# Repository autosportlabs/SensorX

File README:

DESCRIPTION:

SensorX is a breakout board designed to make it easy to integrate sensors to the analog 
inputs of RaceCapture. 

7 channels are supported to match the inputs of RaceCapture. Pullup resistors are included 
on all channels to enable resistive sensors such as temperature & fuel level; these resistors 
can be disabled by cutting traces.

Multiple ground and 5v voltage references are also provided.

The board is sized to be finished with shrink-tubing and installed in-line with wiring harness
bundles, so no explicit mounting or enclosures are necessary!

LICENSE:

The technical artifacts provided in this project is covered in a modified version of the
Creative Commons BY-SA license - see the LICENSE file for the full text.

MORE INFO:

for more information visit http://www.autosportlabs.net

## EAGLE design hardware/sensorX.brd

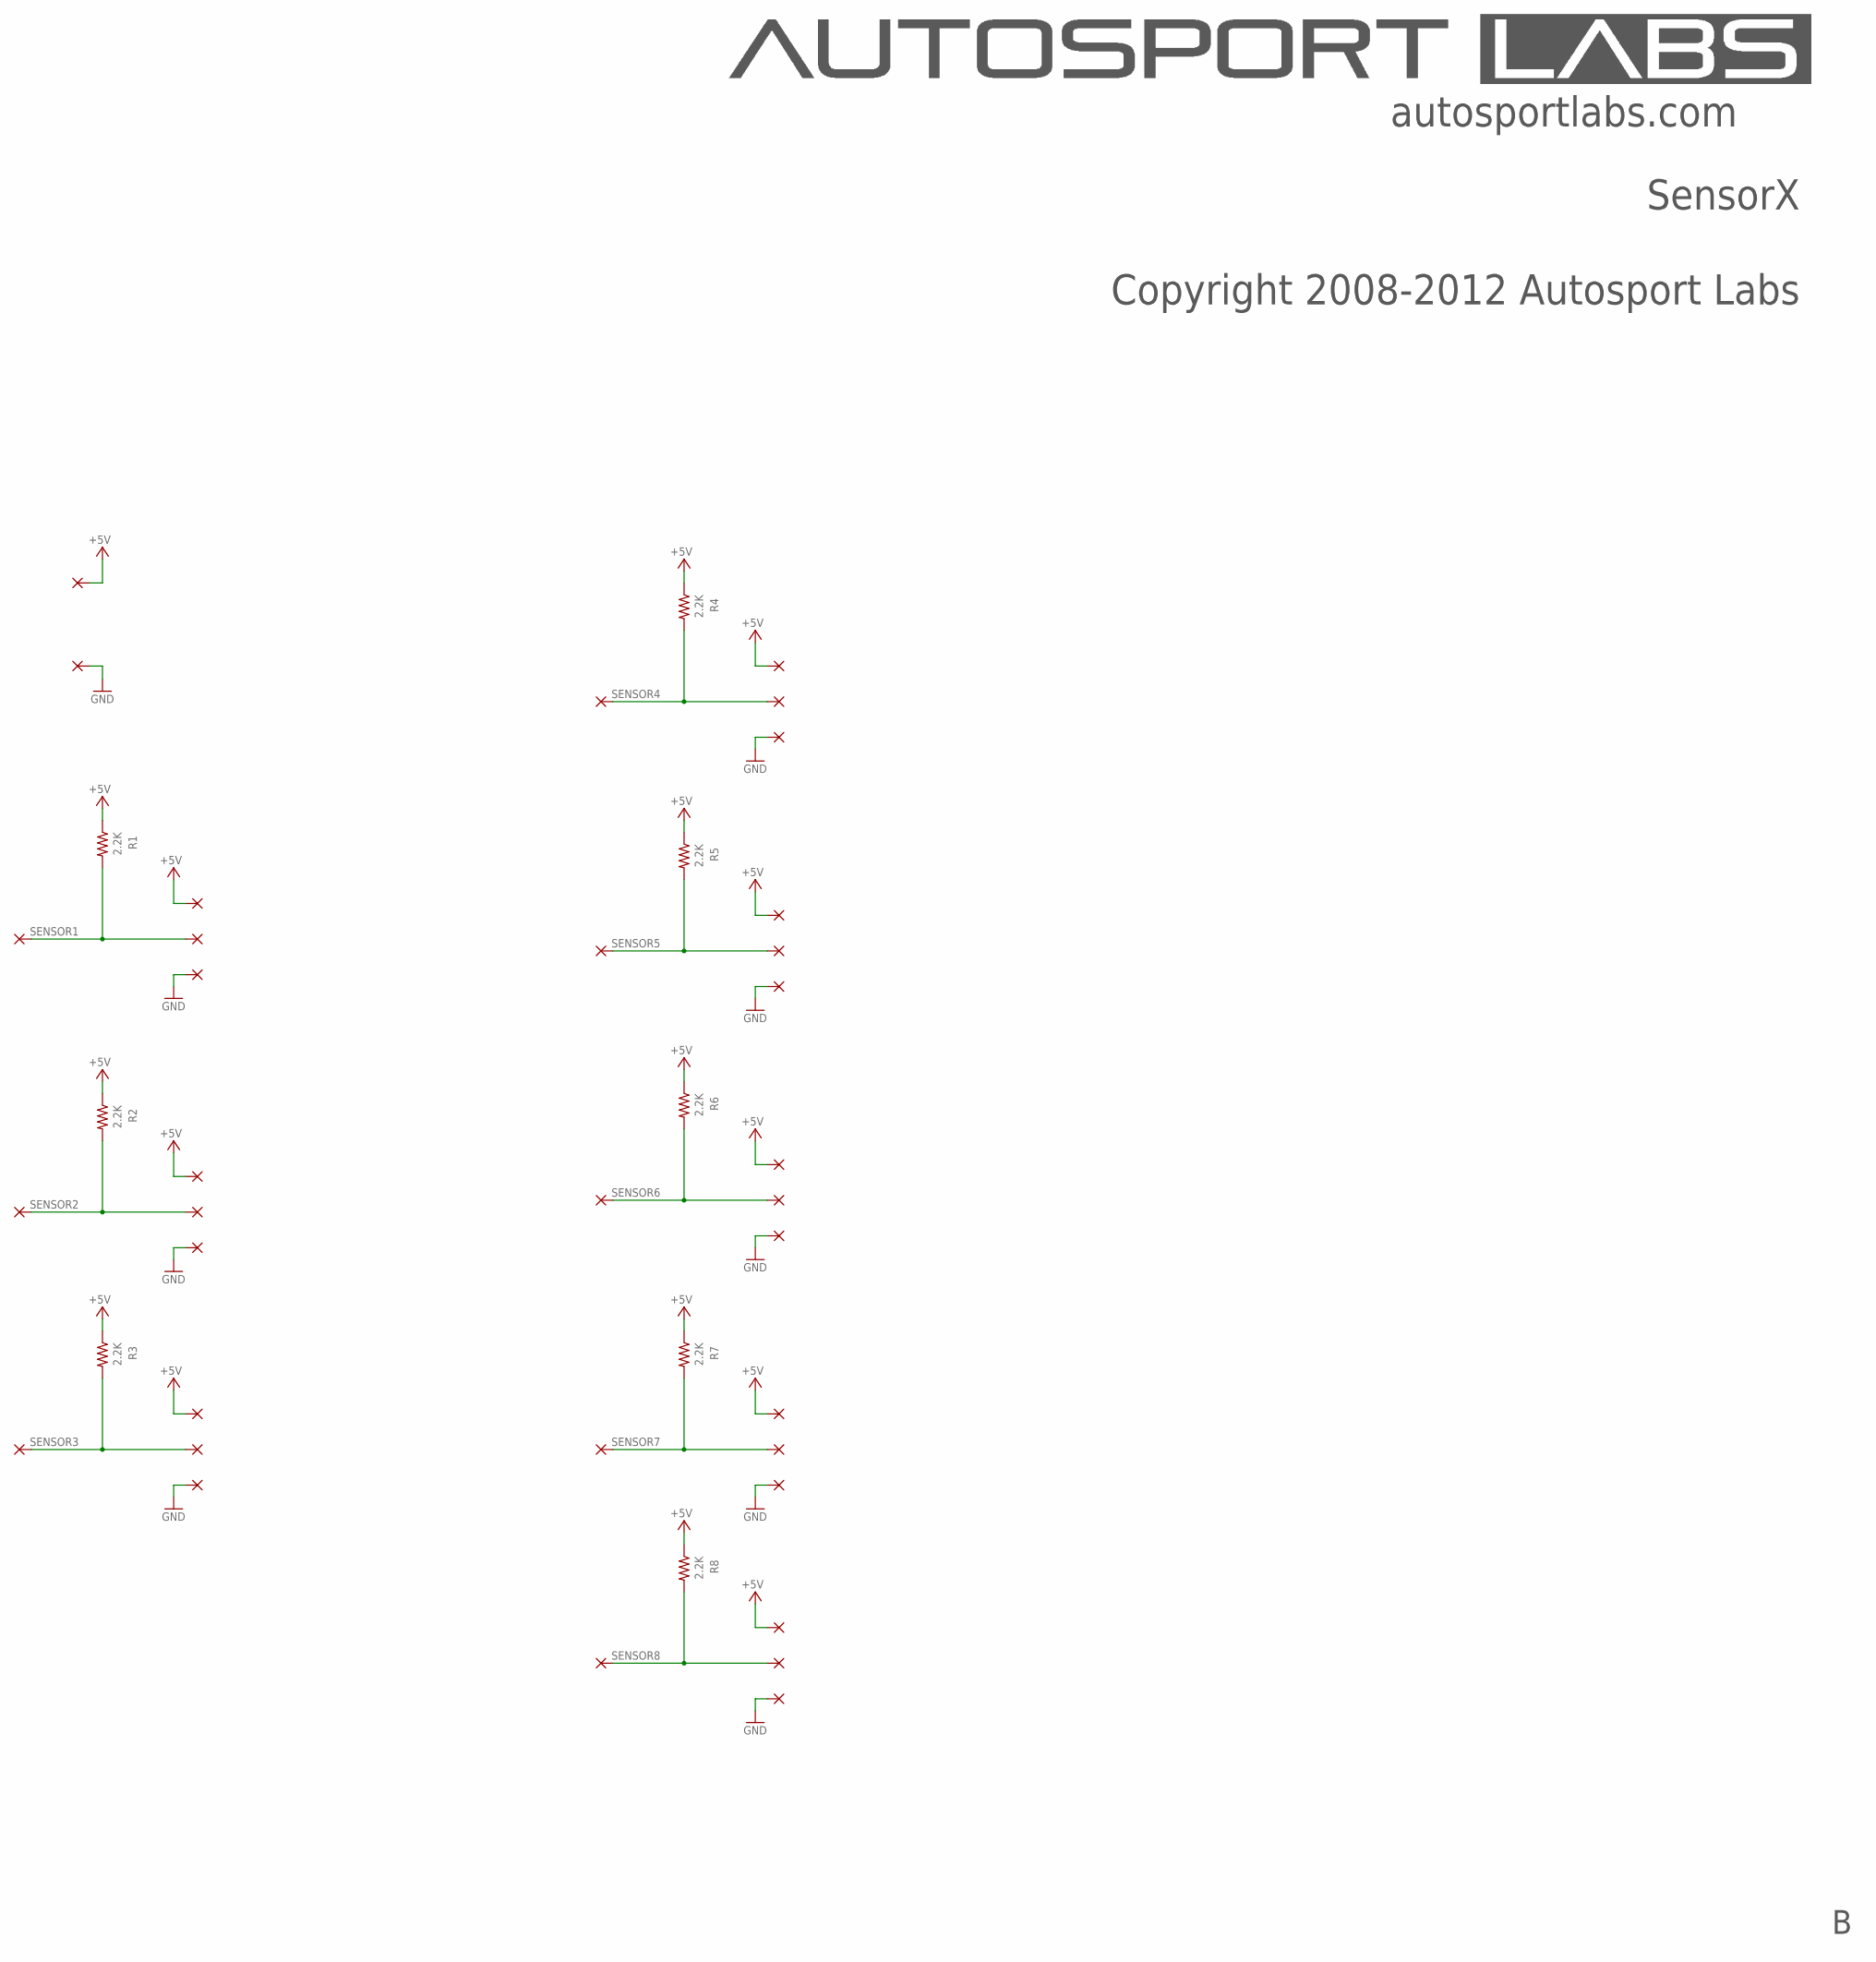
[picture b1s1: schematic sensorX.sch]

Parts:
1, 2, 3, 4, 5, 5V, 5V_1, 5V_2, 5V_3, 5V_4, 5V_5, 5V_6, 5V_7, 5V_8, 6, 7, 7_IN, 8, 8_IN: WIREPAD3,17/1,2; 3,17/1,2
GND: WIREPAD3,17/1,2; 3,17/1,2
GND-1: WIREPAD3,17/1,2; 3,17/1,2
GND_2, GND_3, GND_4, GND_5, GND_6, GND_7, GND_8: WIREPAD3,17/1,2; 3,17/1,2
IN_1, IN_2, IN_3, IN_4, IN_5, IN_6: WIREPAD3,17/1,2; 3,17/1,2
R1, R2, R3, R4, R5, R6, R7, R8: 2.2K; 0204/5

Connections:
+5V: 5V.1, 5V_1.1, 5V_2.1, 5V_3.1, 5V_4.1, 5V_5.1, 5V_6.1, 5V_7.1, 5V_8.1, R1.1, R2.1, R3.1, R4.1, R5.1, R6.1, R7.1, R8.1
GND: GND.1, GND-1.1, GND_2.1, GND_3.1, GND_4.1, GND_5.1, GND_6.1, GND_7.1, GND_8.1
SENSOR1: 1.1, IN_1.1, R1.2
SENSOR2: 2.1, IN_2.1, R2.2
SENSOR3: 3.1, IN_3.1, R3.2
SENSOR4: 4.1, IN_4.1, R4.2
SENSOR5: 5.1, IN_5.1, R5.2
SENSOR6: 6.1, IN_6.1, R6.2
SENSOR7: 7.1, 7_IN.1, R7.2
SENSOR8: 8.1, 8_IN.1, R8.2

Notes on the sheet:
Copyright 2008-2012 Autosport Labs
SensorX
autosportlabs.com

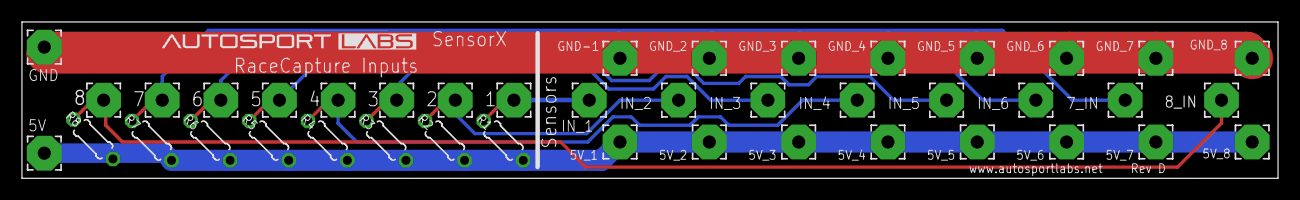
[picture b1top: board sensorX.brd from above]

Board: 2 copper layers, 114.3 x 14.2 mm, 42 parts (0 on the bottom side), 10 nets.

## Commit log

2012-03-29 added folders
2012-03-29 schematics and beginnings of SensorX board
2012-03-30 Rev A candidate for Sensor Xpansion board
2012-03-30 changed breakable jumpers to thin traces
2012-03-30 added fiducial marks
2012-04-06 added OSHW logo
2012-04-06 shrank size; changed cap value
2012-04-08 fixed typo
2014-09-17 changed SMT pullup resistors to through-hole, cleaned up design
2014-09-17 updated image
2014-09-17 removed fiducial marks
2014-09-17 shrunk board
2016-04-16 fixed overlap
2018-04-04 add 8th sensor position
2018-04-04 update image
